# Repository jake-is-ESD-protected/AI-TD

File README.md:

# AI-TD
***Transient designer with analog circuitry, digital control and AI assisted enhancement!***

## About
AI-TD is a unique approach to transient shaping. This project utilizes the **Daisy Seed** by **Electrosmith** as a powerful embedded system for audio within a guitar pedal. On command it samples the user's instrument signal and estimates a suggested transient shaping by employing an **embedded AI**

|Key-Facts||
|-|-|
|Platform:|**Daisy Seed by Electrosmith**|
|Chipset:|**STM32H7 family**|
|AI:|**Driven by RTNeural**|
|AI-Model:|**Selfmade, see Taunet Folder**|
|Effect:|**Transient shaping**|
|Further Infos and Demo:|**[*here*](https://kristof-konya.dev/projects/AITD)**|

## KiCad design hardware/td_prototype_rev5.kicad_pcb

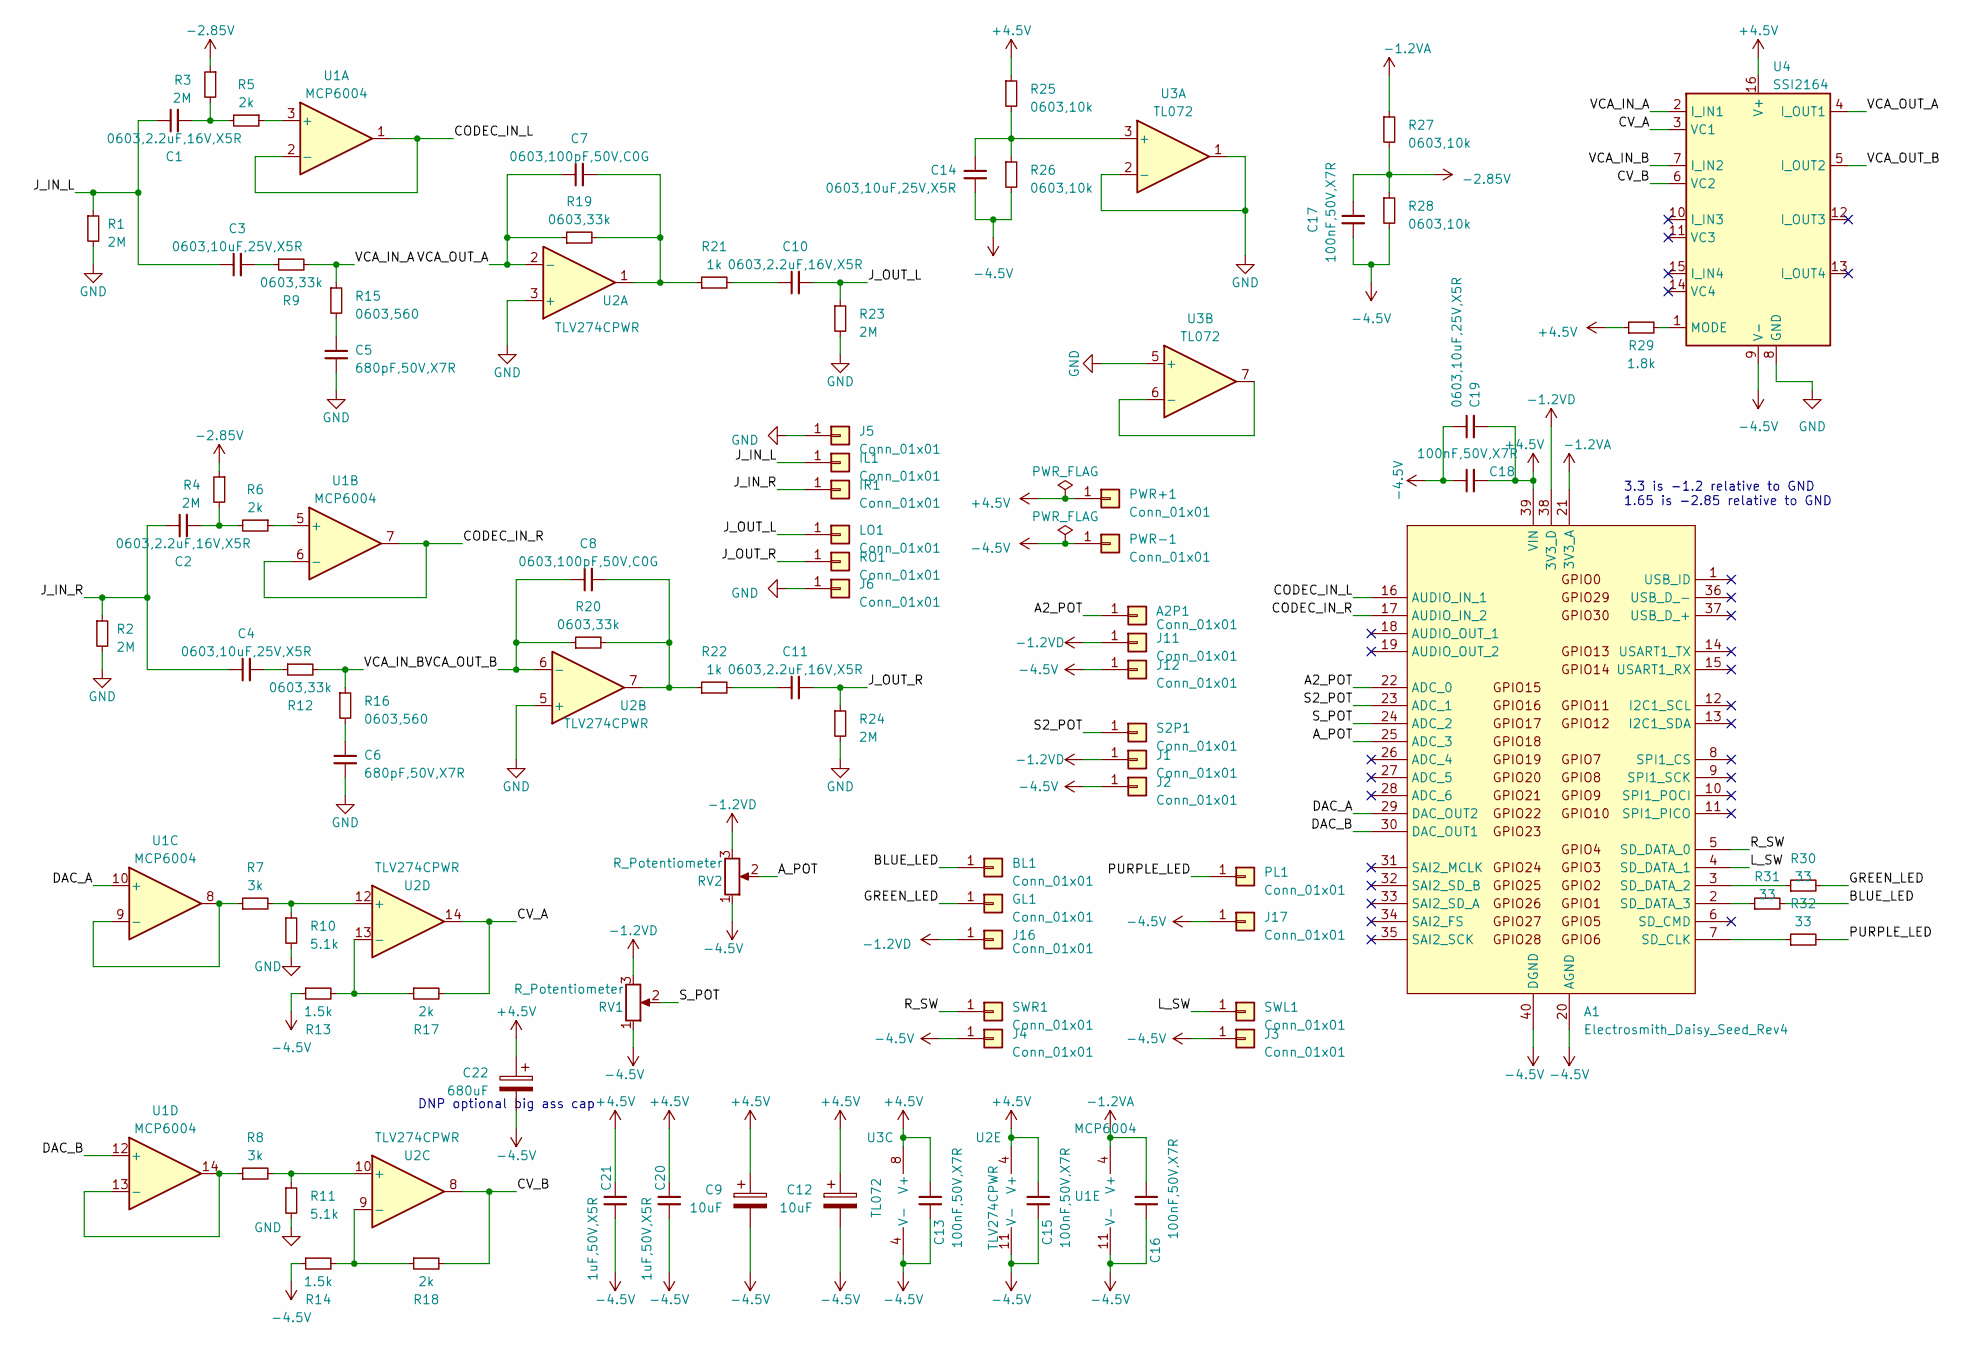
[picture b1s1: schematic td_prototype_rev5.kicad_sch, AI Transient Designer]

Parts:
A1: Electrosmith_Daisy_Seed_Rev4; Electrosmith_Daisy_Seed
A2P1: Conn_01x01; Solder_Hole_Oval
BL1: Conn_01x01; Solder_Hole_Oval
C1, C2, C10, C11: 0603,2.2uF,16V,X5R; C_0603_1608Metric; MFGPN CL10A225KO8NNNC; LCSC C23630
C3, C4, C14, C19: 0603,10uF,25V,X5R; C_0603_1608Metric; MFGPN CL10A106MA8NRNC; LCSC C96446
C5, C6: 680pF,50V,X7R; C_0603_1608Metric; MFGPN 0603B681K500NT; LCSC C1630
C7, C8: 0603,100pF,50V,C0G; C_0603_1608Metric; MFGPN CL10C101JB8NNNC; LCSC C14858
C9, C12: 10uF; CP_Elec_6.3x7.7; LCSC C72482
C13, C15, C16, C17, C18: 100nF,50V,X7R; C_0603_1608Metric; MFGPN CC0603KRX7R9BB104; LCSC C14663
C20, C21: 1uF,50V,X5R; C_0603_1608Metric; MFGPN CL10A105KB8NNNC; LCSC C15849
C22: 680uF; CP_Radial_D8.0mm_P3.80mm
GL1: Conn_01x01; Solder_Hole_Oval
IL1: Conn_01x01; Solder_Hole_Oval
IR1: Conn_01x01; Solder_Hole_Oval
J1, J11, J16: Conn_01x01; Solder_Hole_Rounded_Square
J2, J3, J4, J5, J6, J12, J17: Conn_01x01; Solder_Hole_Square
LO1: Conn_01x01; Solder_Hole_Oval
PL1: Conn_01x01; Solder_Hole_Oval
PWR+1: Conn_01x01; Solder_Hole_Rounded_Square
PWR-1: Conn_01x01; Solder_Hole_Square
R1, R2, R3, R4, R23, R24: 2M; R_0603_1608Metric; MFGPN 0603WAF2004T5E; LCSC C22976
R5, R6, R17, R18: 2k; R_0603_1608Metric; MFGPN 0603WAF2001T5E; LCSC C22975
R7, R8: 3k; R_0603_1608Metric; MFGPN 0603WAF3001T5E; LCSC C4211
R9, R12, R19, R20: 0603,33k; R_0603_1608Metric; MFGPN 0603WAF3302T5E; LCSC C4216
R10, R11: 5.1k; R_0603_1608Metric; MFGPN 0603WAF5101T5E; LCSC C23186
R13, R14: 1.5k; R_0603_1608Metric; MFGPN 0603WAF1501T5E; LCSC C22843
R15, R16: 0603,560; R_0603_1608Metric; MFGPN 0603WAF5600T5E; LCSC C23204
R21, R22: 1k; R_0603_1608Metric; MFGPN 0603WAF1001T5E; LCSC C21190
R25, R26, R27, R28: 0603,10k; R_0603_1608Metric; MFGPN 0603WAF1002T5E; LCSC C25804
R29: 1.8k; R_0603_1608Metric; MFGPN 0603WAF1801T5E; LCSC C4177
R30, R31, R32: 33; R_0603_1608Metric; MFGPN 0603WAF330JT5E; LCSC C23140
RO1: Conn_01x01; Solder_Hole_Oval
RV1, RV2: R_Potentiometer; Potentiometer_Alpha_RD901F-40-00D_Single_Vertical_CircularH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
S2P1: Conn_01x01; Solder_Hole_Oval
SWL1: Conn_01x01; Solder_Hole_Oval
SWR1: Conn_01x01; Solder_Hole_Oval
U1: MCP6004; SOIC-14_3.9x8.7mm_P1.27mm; LCSC C7378
U2: TLV274CPWR; TSSOP-14_4.4x5mm_P0.65mm; LCSC C9914
U3: TL072; SOP-8_3.9x4.9mm_P1.27mm; LCSC C67473
U4: SSI2164; DIP-16_W7.62mm_Socket

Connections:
+4.5V: A1.39 (VIN), C9.1, C12.1, C13.1, C15.1, C18.2, C19.2, C20.2, C21.2, C22.1, PWR+1.1, R25.1, R29.1, U2.4 (V+), U3.8 (V+), U4.16 (V+)
-1.2VA: A1.21 (3V3_A), C16.1, R27.1, U1.4 (V+)
-1.2VD: A1.38 (3V3_D), J1.1, J11.1, J16.1, RV1.3, RV2.3
-2.85V: C17.1, R3.1, R4.1, R27.2, R28.1
-4.5V: A1.20 (AGND), A1.40 (DGND), C9.2, C12.2, C13.2, C14.1, C15.2, C16.2, C17.2, C18.1, C19.1, C20.1, C21.1, C22.2, J2.1, J3.1, J4.1, J12.1, J17.1, PWR-1.1, R13.1, R14.1, R26.2, R28.2, RV1.1, RV2.1, U1.11 (V-), U2.11 (V-), U3.4 (V-), U4.9 (V-)
/A2_POT: A1.22 (ADC_0), A2P1.1
/A_POT: A1.25 (ADC_3), RV2.2
/BLUE_LED: BL1.1, R31.2
/CODEC_IN_L: A1.16 (AUDIO_IN_1), U1.1, U1.2 (-)
/CODEC_IN_R: A1.17 (AUDIO_IN_2), U1.6 (-), U1.7
/CV_A: R17.2, U2.14, U4.3 (VC1)
/CV_B: R18.2, U2.8, U4.6 (VC2)
/DAC_A: A1.29 (DAC_OUT2), U1.10 (+)
/DAC_B: A1.30 (DAC_OUT1), U1.12 (+)
/GREEN_LED: GL1.1, R30.2
/J_IN_L: C1.1, C3.1, IL1.1, R1.1
/J_IN_R: C2.1, C4.1, IR1.1, R2.1
/J_OUT_L: C10.2, LO1.1, R23.1
/J_OUT_R: C11.2, R24.1, RO1.1
/L_SW: A1.4 (SD_DATA_1), SWL1.1
/PURPLE_LED: PL1.1, R32.2
/R_SW: A1.5 (SD_DATA_0), SWR1.1
/S2_POT: A1.23 (ADC_1), S2P1.1
/S_POT: A1.24 (ADC_2), RV1.2
/VCA_IN_A: R9.2, R15.1, U4.2 (I_IN1)
/VCA_IN_B: R12.2, R16.1, U4.7 (I_IN2)
/VCA_OUT_A: C7.1, R19.1, U2.2 (-), U4.4 (I_OUT1)
/VCA_OUT_B: C8.1, R20.1, U2.6 (-), U4.5 (I_OUT2)
GND: C5.2, C6.2, J5.1, J6.1, R1.2, R2.2, R10.2, R11.2, R23.2, R24.2, U2.3 (+), U2.5 (+), U3.1, U3.2 (-), U3.5 (+), U4.8 (GND)
unnamed: A1.7 (SD_CLK), R32.1
unnamed: A1.3 (SD_DATA_2), R30.1
unnamed: A1.2 (SD_DATA_3), R31.1
unnamed: C1.2, R3.2, R5.2
unnamed: C2.2, R4.2, R6.2
unnamed: C3.2, R9.1
unnamed: C4.2, R12.1
unnamed: C5.1, R15.2
unnamed: C6.1, R16.2
unnamed: C7.2, R19.2, R21.1, U2.1
unnamed: C8.2, R20.2, R22.1, U2.7
unnamed: C10.1, R21.2
unnamed: C11.1, R22.2
unnamed: R5.1, U1.3 (+)
unnamed: R6.1, U1.5 (+)
unnamed: R7.1, U1.8, U1.9 (-)
unnamed: R8.1, U1.13 (-), U1.14
unnamed: R8.2, R11.1, U2.10 (+)
unnamed: R14.2, R18.1, U2.9 (-)
unnamed: R7.2, R10.1, U2.12 (+)
unnamed: R13.2, R17.1, U2.13 (-)
unnamed: C14.2, R25.2, R26.1, U3.3 (+)
unnamed: U3.6 (-), U3.7
unnamed: R29.2, U4.1 (MODE)

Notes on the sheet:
3.3 is -1.2 relative to GND 1.65 is -2.85 relative to GND
DNP optional big ass cap

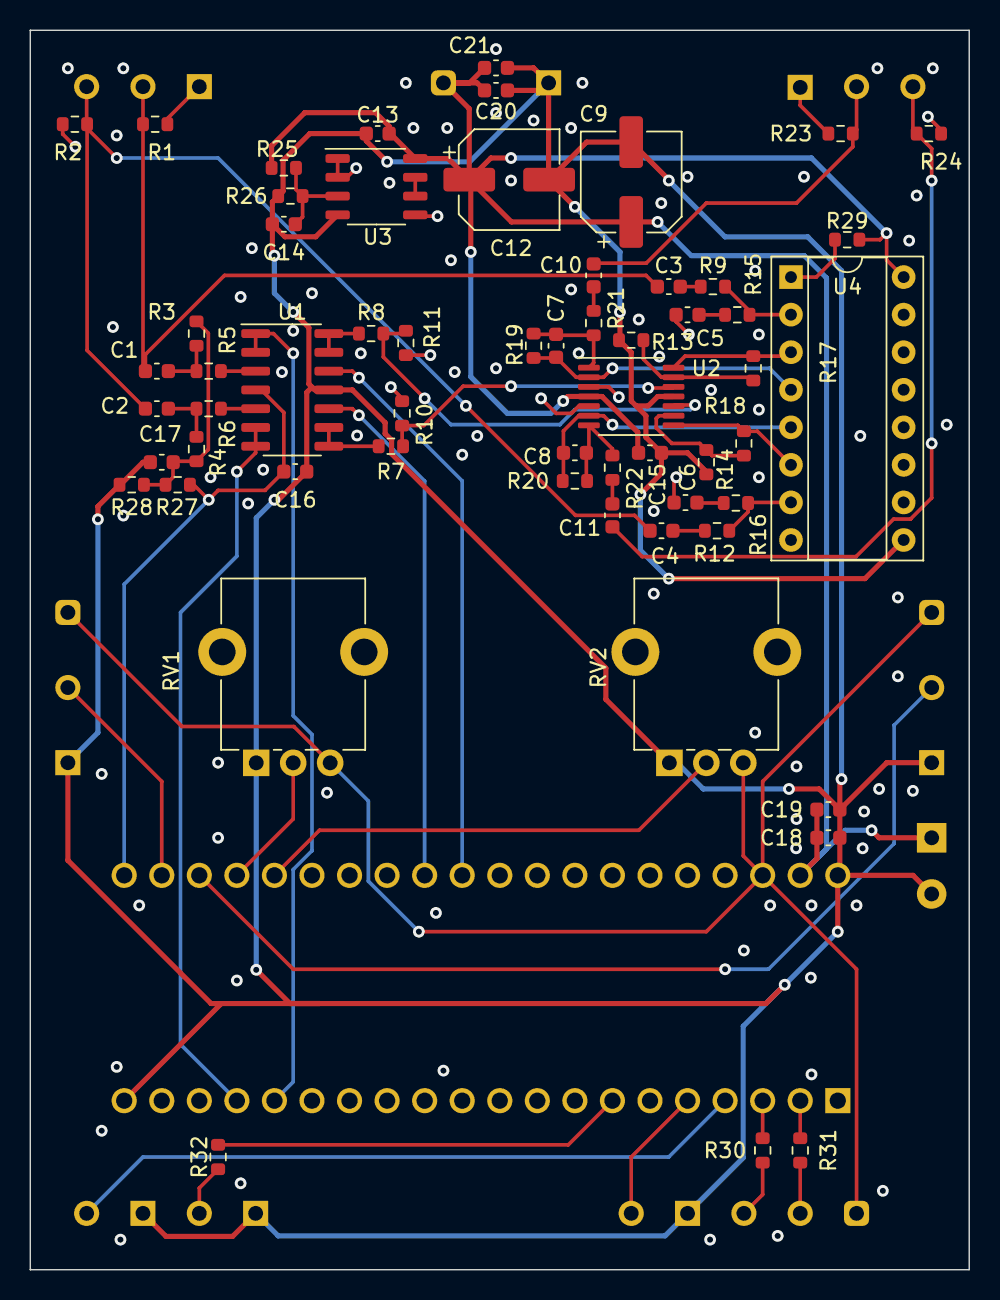
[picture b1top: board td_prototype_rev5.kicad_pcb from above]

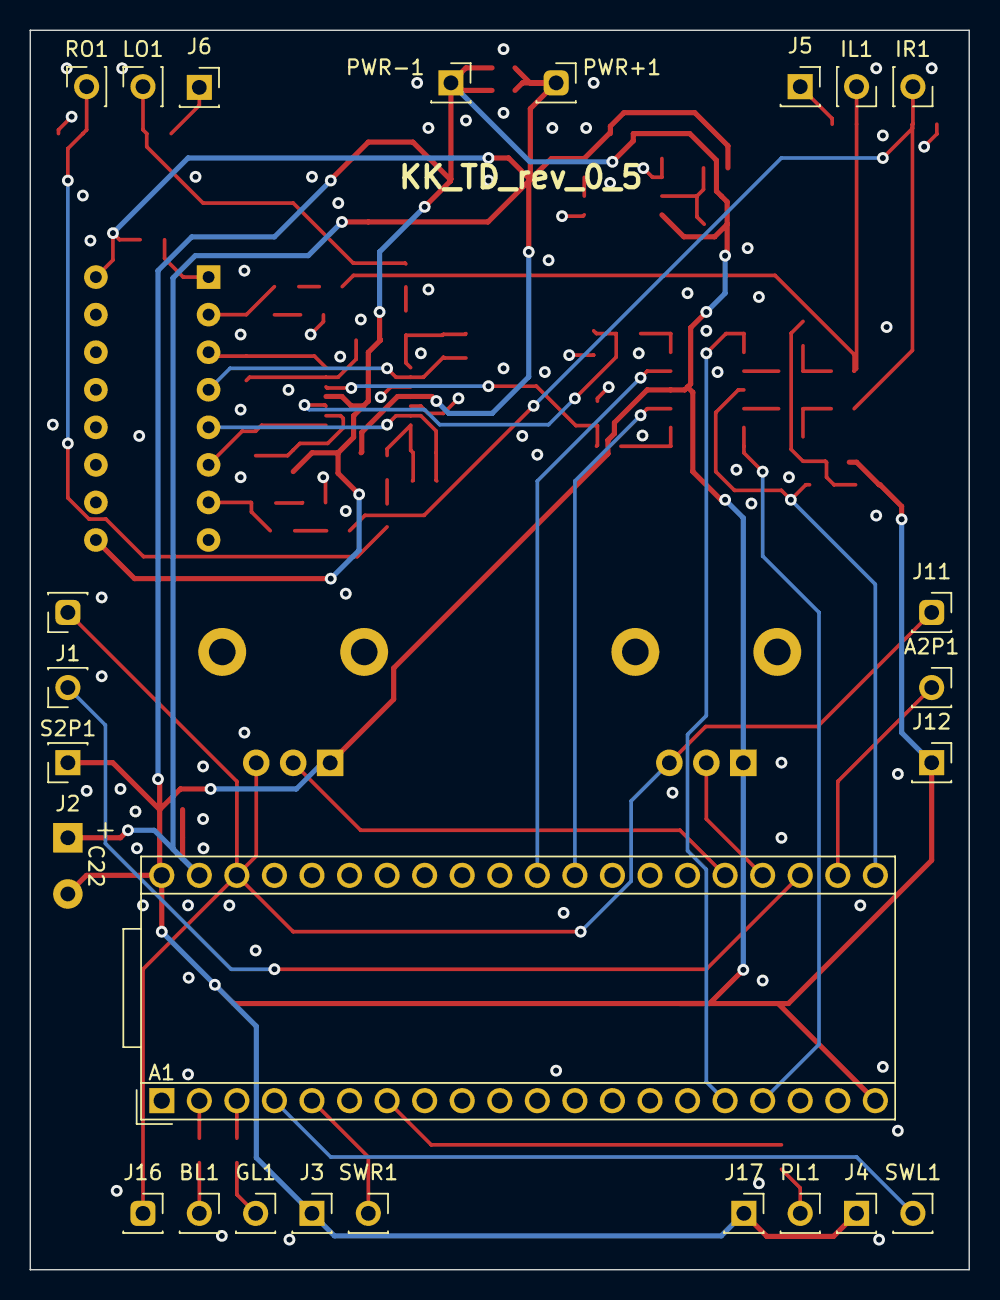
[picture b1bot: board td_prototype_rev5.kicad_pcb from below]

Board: 4 copper layers, 63.5 x 83.8 mm, 84 parts (25 on the bottom side), 53 nets.

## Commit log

2023-10-20 init commit of first working draft
2023-10-20 gitignore fix
2023-10-20 oh fuck it still doesnt work
2023-10-20 setup is done
2023-10-21 redo folder structure
2023-10-21 modified folder structure
2023-10-21 add include flags
2023-10-21 rm .vscode from git tracking
2023-10-21 add basic tester model
2023-10-21 edit example to blink with approximated result speed
2023-10-22 bump gccarmnoneeabi version to 1.9 for compilation on raspberry pi
2023-10-22 adjusted makefile to new folder struct + moved weigths into sdram + commited library
2023-10-22 0 to 2Pi inference on network weigths from qspi flash
2023-10-23 add notes on xcubeai driver lib
2023-10-23 rm depr lib path
2023-10-23 start some docs
2023-10-23 update README, closes #3
2023-10-23 empty files for mini CLI
2023-10-24 setup breadboard protobench rev0_1 + libk needs to be included now + the setup is K1:LFO Speed K2:LF Amt K3 - K4:DC Offset for basic VCA control
2023-10-24 clean up + extra files for hal
2023-10-24 added transientDSP structure for signal conditioning and CV calculation + ui with Knob abstraction class from libk
2023-10-26 First very ugly import of a working transient designer
2023-10-26 half broken but code is more tweakable will continue tmrw with a fresh mind
2023-10-27 found the worm finding max in CircularBuffer took too long + reduced buffer size for now working on a new approach
2023-10-27 block processing helped making a buffer of 512 functional
2023-10-27 moved some shit into seperate folder + fixed the env follower buff size with a macro
2023-10-27 setup a basic differntial attack stage + timeconstant ui assignment logic cleanup
2023-10-27 clang setup
2023-10-27 functional transient designer with variable time contants but untuned (scope tuned) gain stages
2023-10-27 started to musically evaluate the envlopes and jesus they are tasty
2023-10-28 tuning zem enveloeps and adding led feedback + bypass switch
2023-10-28 add libK
2023-10-28 depend on daisySP
2023-10-28 enabled boost mode
2023-10-28 removed daisySP + added timers and seperate callbacks for UI and visuals
2023-10-29 rm daisySP deps
2023-10-29 fix include errors
2023-10-29 add simple write/read methods for CLI
2023-10-29 init CLI routine
2023-10-29 force monitor port
2023-11-01 rm hardcoded monitor port
2023-11-01 move cli init to hal init
2023-11-01 move cli to own module
2023-11-01 declare cli parse and pipe
2023-11-01 refactor according to issue #19
2023-11-01 move all hw related stuff to hal
2023-11-02 disable debug optimization
2023-11-02 add parser
2023-11-02 experiment with python serial port handling
2023-11-02 disable audio callback (temporary)
2023-11-02 create future shell script for seedcli invocation
2023-11-04 modified makefile so project builds again
2023-11-05 changed behaviour of which sustain envelope time constant should be controllable
2023-11-07 working base communication from cli
2023-11-07 add linux bridge script
2023-11-07 add windows bridge script
2023-11-15 add seedcli submodule
2023-11-15 WIP TEST COMMIT
2023-11-22 add seedcli client as submodule
2023-11-22 reintroduce vscode jsons
2023-11-22 depend on env vars for lib paths
2023-11-22 rm pio from project
2023-11-22 reinclude libs after sanity check push
2023-11-23 seedcli.py update
2023-11-23 change depr args
2023-11-23 add cortex debug
2023-11-23 make includes local
2023-11-23 fix newline issue
2023-11-23 local includes
2023-11-23 add sdram write and EOF detection
2023-11-23 add mem related macros
2023-11-23 huh?
2023-11-23 working approach with crc 😎
2023-12-03 fix intellisense include errors
2023-12-03 hex format switch
2023-12-03 move all hw stuff to hal, introduce cli-server function
2023-12-03 add wrappers for other submodules to use
2023-12-03 working qspi flashing
2023-12-03 tiny adjustment in cv scaling for new bipolar power delivery scheme
2023-12-06 intellisense include fix for libdaisy
2023-12-06 include path fix
2023-12-06 enable boost mode
2023-12-06 disable audio on cli idle entry
2023-12-06 refactor to decouple cli module
2023-12-06 add seedcli as external library
2023-12-08 modified folder structure and paths
2023-12-08 different include paths
2023-12-08 rm ai stuff
2023-12-08 ai module template
2023-12-08 move ai libs to other folder
2023-12-12 fix locality error in makefile
2023-12-12 add halLEDset to ai error routine
2023-12-19 taunet explorative research
2023-12-23 started evaling PCB
2023-12-24 added new proper pin remapping for pcb rev_05
2023-12-24 light + CV Proto Assembly TestBench
2023-12-24 added buttons to testbench build
2023-12-25 Transient Designer goess brrr
2024-01-08 calibrated for 0dBu i/o
2024-01-08 in between push
2024-01-08 FIXED EVERY FUKIN THING
2024-01-18 add measurements
2024-01-18 export plots
2024-01-25 redo plots for report
2024-01-26 add ai to startup
2024-01-26 update seedcli
2024-01-27 removed timer and handled all the stuff in the audio callback + added O2 optmimization flag
2024-01-27 post initial tuning with luka
2024-02-01 demo feature exploration
2024-02-04 prepping for initial tuning session
2024-02-13 post tuning luka
2024-02-24 UI retuning
2024-03-04 demo audio features
2024-03-05 explore more features
2024-03-06 random end of session commit
2024-03-06 fixed header issues
2024-03-06 Improved gitignore
2024-03-06 removed existing .wav files for consistency reasons
2024-03-08 add RTNeural submodule
2024-03-08 define AF getters, compile and upload
2024-03-08 rm legacy stuff
2024-03-08 Merge branch 'JT_AI_abstraction' into KK_0_5_rev_PCB_EVAL
    # Conflicts:
    # src/hal/hal.cpp
2024-03-08 SIEG
2024-03-10 incomplete port need from cpp 2 c for Smoother exponential or better makefile setup that supports linking between c and cpp
2024-03-11 small little panic commit mid session
2024-03-11 end of session push
2024-03-12 cleanup legacy shit
2024-03-12 bugfixing and add debug helpers
2024-03-12 visual verification of C code in python
2024-03-16 on my way to adding peakhold for more robustness
2024-03-16 adding peak hold and percentile schemes to improve analytical detection
2024-03-18 smaller improvements to af feature extraction
2024-03-18 bugfix to get it working again
2024-03-18 end of session comments
2024-03-20 randomly optimize some stuff and now the CLI callback works???
2024-03-22 Making shit more efficient for the cli
2024-03-22 seedcli reads out knobs
2024-03-22 aft getter implemented
2024-04-04 end of session STFT port succesfull
2024-04-13 random seedcli submodule footprint update
2024-04-13 add spectral centroid
2024-04-13 add spectral flatness (need data normalization)
2024-04-13 forgot to update submodules
2024-04-15 fixed spectral flatness
2024-04-15 moved af dsp to seperate file and added all the stubs for the ipynb
2024-04-17 added shift layer reset functionality
2024-04-17 updated seedcli for csv gen
2024-04-20 rm old audiofeature notebook
2024-04-20 outsource audio reader to new utils file
2024-04-20 ignore pycache
2024-04-20 remove legacy measurements
2024-04-20 update utils
2024-04-20 get input data as dict
2024-04-20 pretty print input data
2024-04-22 added new measurement id system
2024-04-23 added spectral flux af
2024-04-25 ignore csv
2024-04-25 add pandas
2024-04-25 add dataset structure
2024-04-25 dataset creation notebook
2024-04-25 ignore logs
2024-04-25 create a super bad non functional net for conversion testing
2024-04-25 tune taunet
2024-04-26 added remove rule for dll outpute file on clean
2024-04-26 added eq bands and audio buffer normalisation but eq normalisation is quiet off
2024-04-26 depend on saved data
2024-04-27 add model saver in json and save to appropriate log dir
2024-04-29 intellisense include RTNeural
2024-04-29 data analysis push
2024-04-29 end of session, crest factor, magnitude normalization, spectral centroid fix, libroas setup
2024-05-02 one more run
2024-05-02 add human taus to visualizer
2024-05-02 add static model parser json2h
2024-05-02 autogen model arrays
2024-05-02 migrate to RTNeural. Closes RTNeural Setup #57 and Migrate to RTNeural #33
2024-05-05 crude normalization of data (range 0...1)
2024-05-05 convert model
2024-05-06 issue, vector table bus faul
2024-05-06 vector table bus fault
2024-05-07 first test by simply increasing attack release tau
2024-05-08 add augmolino
2024-05-08 transpose weights
2024-05-08 working rtneural and dsp
2024-05-08 TD attack flutter fix at loosing the snappyness :( I need to find a better approach, tradeoffs need to be made
2024-05-09 proper attack compensation scheme implemented
2024-05-09 detect AFinC deaths and log steps
2024-05-09 augmentation run!
2024-05-13 improved and smaller model!
2024-05-13 manual network fix
2024-05-13 retrain model fix
2024-05-13 ai finally fuckn works on plattform
2024-05-13 added qspi flash loader project
2024-05-13 reduced flash size by taking out bunch of stuff for qspi experimentation and setup af target includes
2024-05-13 flash loading proof of concept
2024-05-15 edited gitignore for for first session with luka
2024-05-15 made functional data gathering possible
2024-05-15 gitignore for wav files
2024-05-20 enabled the slowsine calculation the BTT algo and won 9% flash space yipeeee
2024-05-20 debugging is possible again and transient dsp is back up and running
2024-05-20 qspiFlash loader work in progress
2024-05-21 added gitignore for easy branch switching
2024-05-23 added adcIn for future hardware oversampling of audio in
2024-05-23 split attack gain into attack boost and cut
2024-05-23 new run with less parameters and new dataset. RMSE=0.14
2024-05-27 end of session the earth is flat now
2024-05-27 QSPI loading succesfull
2024-06-03 added max for TA1 and TA2
2024-06-03 working af but very slow
2024-06-03 removed random ass return
2024-06-04 working processing while recording but still way to slow
2024-06-06 lowering sampling rate temporarely for beat detection
2024-06-07 better normalization, add luka dataset
2024-06-10 changed sample rate of afs to 48k
2024-06-11 correct, normalized dataset, new models for kristof and luka
2024-06-12 added cancelation method on shift layer use
2024-06-12 working inference with new model from qspi flash
2024-06-12 Target Inferencing numerically coherent
2024-06-12 on target on input inferencing sucessfull
2024-06-12 forced the ais output as time constants
2024-06-12 added proper cancelation scheme
2024-06-14 ported whole project to float
2024-06-14 sweet little only calculate tempo till we get first valid number scheme :)
2024-06-14 moved UI/UX rendering to timer based callback
2024-06-14 first ux sketch
2024-06-15 add default tempo for 0 cases
2024-06-15 switch to specific python side AFinC process function
2024-06-15 another retrain
2024-06-15 Added all knobs as cancelation option for AI
2024-06-15 better AF plots
2024-06-15 proper UI/UX scheme for ai Handlin
2024-06-15 added new weights and [LUKA]
2024-06-16 sustain HF split
2024-06-16 new dataset with sustain HF split
2024-06-16 new taunet with sustain HF split
2024-06-17 removed old weight file
2024-06-17 demo for LNDW
2024-06-17 added startup animation
2024-06-18 leave aiMode on bypass
2024-06-22 further improved visuals for LNDW
2024-06-23 fixed ai receiving data animation and refractoring a shitton
2024-07-01 fetch timings firmware
2024-07-01 removed falsy placed resets
2024-07-10 added sub2rec feature
2025-03-21 added hardware files
2025-03-21 added example video to repo
2025-03-21 edited readme
2025-03-21 readme edit
2025-03-23 added RMSE offset experiment
